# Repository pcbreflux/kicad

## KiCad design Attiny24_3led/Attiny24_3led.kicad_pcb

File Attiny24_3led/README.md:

ATtiny24 3 LED Demo
===========================
Application: kicad
Version: 5.0.0-rc2-unknown-228881f~65~ubuntu18.04.1, release build

Nightly Development Builds

	sudo add-apt-repository --yes ppa:js-reynaud/ppa-kicad
	sudo apt update
	sudo apt install kicad

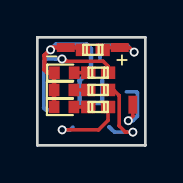
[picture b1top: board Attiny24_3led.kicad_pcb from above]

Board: 2 copper layers, 6.0 x 6.0 mm, 11 parts (1 on the bottom side), 9 nets.

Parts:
C1: C; c_0402
D1, D2, D3: LED_Small; LED_0402
J4, J5, J6: TEST_1P; SolderWirePad_single_SMD_1x0.5mm
R1, R2, R3: R; r_0402
U1: ATTINY24A-MU; QFN-20-1EP_4x4mm_Pitch0.5mm

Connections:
+3V3: C1.1, J6.1, U1.9
GND: C1.2, D1.1, D2.1, D3.1, J5.1, U1.8, U1.21
unnamed: D1.2, R1.1
unnamed: D2.2, R2.1
unnamed: D3.2, R3.1
unnamed: J4.1, U1.13
unnamed: R1.2, U1.1
unnamed: R2.2, U1.20
unnamed: R3.2, U1.16

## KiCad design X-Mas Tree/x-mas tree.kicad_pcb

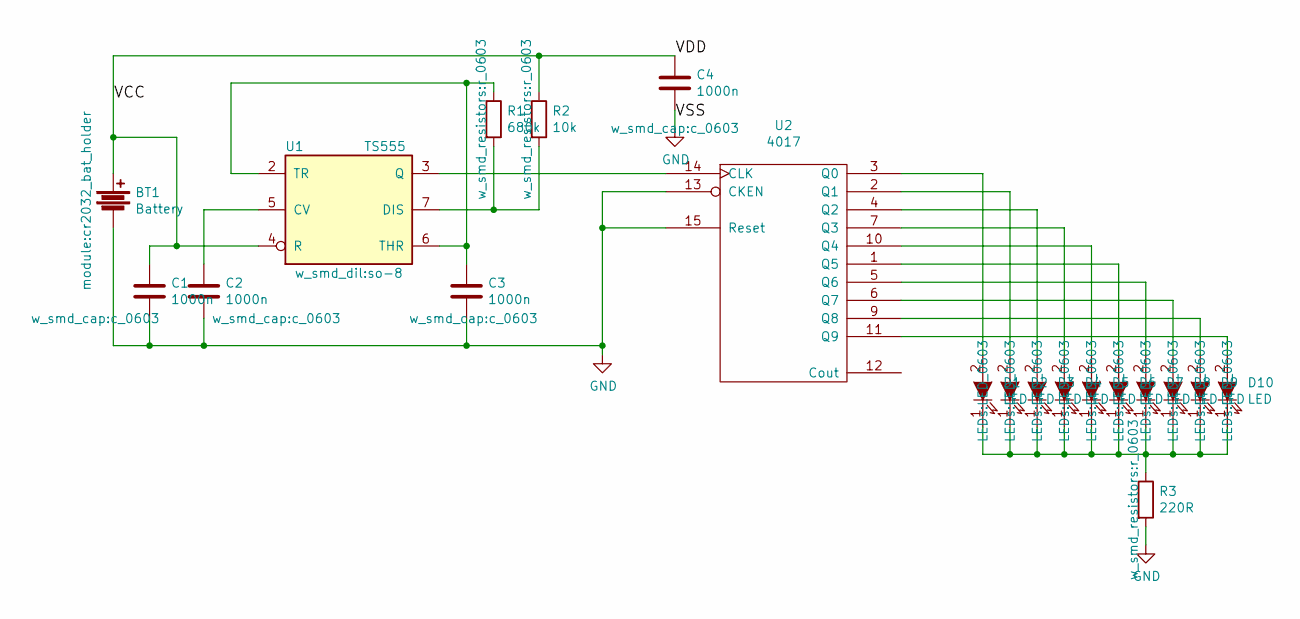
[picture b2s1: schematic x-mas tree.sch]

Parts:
BT1: Battery; cr2032_bat_holder
C1, C2, C3, C4: 1000n; c_0603
D1, D2, D3, D4, D5, D6, D7, D8, D9, D10: LED; LED_0603
R1: 680k; r_0603
R2: 10k; r_0603
R3: 220R; r_0603
U1: TS555; so-8
U2: 4017; sop-16

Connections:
GND: BT1.2, C1.2, C2.2, C3.2, C4.2, R3.2, U1.1 (GND), U2.8 (VSS), U2.13 (CKEN), U2.15 (Reset)
unnamed: C2.1, U1.5 (CV)
unnamed: C3.1, R1.1, U1.2 (TR), U1.6 (THR)
unnamed: D1.1 (K), D2.1 (K), D3.1 (K), D4.1 (K), D5.1 (K), D6.1 (K), D7.1 (K), D8.1 (K), D9.1 (K), D10.1 (K), R3.1
unnamed: D1.2 (A), U2.3 (Q0)
unnamed: D2.2 (A), U2.2 (Q1)
unnamed: D3.2 (A), U2.4 (Q2)
unnamed: D4.2 (A), U2.7 (Q3)
unnamed: D5.2 (A), U2.10 (Q4)
unnamed: D6.2 (A), U2.1 (Q5)
unnamed: D7.2 (A), U2.5 (Q6)
unnamed: D8.2 (A), U2.6 (Q7)
unnamed: D9.2 (A), U2.9 (Q8)
unnamed: D10.2 (A), U2.11 (Q9)
unnamed: R1.2, R2.2, U1.7 (DIS)
unnamed: U1.3 (Q), U2.14 (CLK)
VCC: BT1.1, C1.1, C4.1, R2.1, U1.4 (R), U1.8 (VCC), U2.16 (VDD)

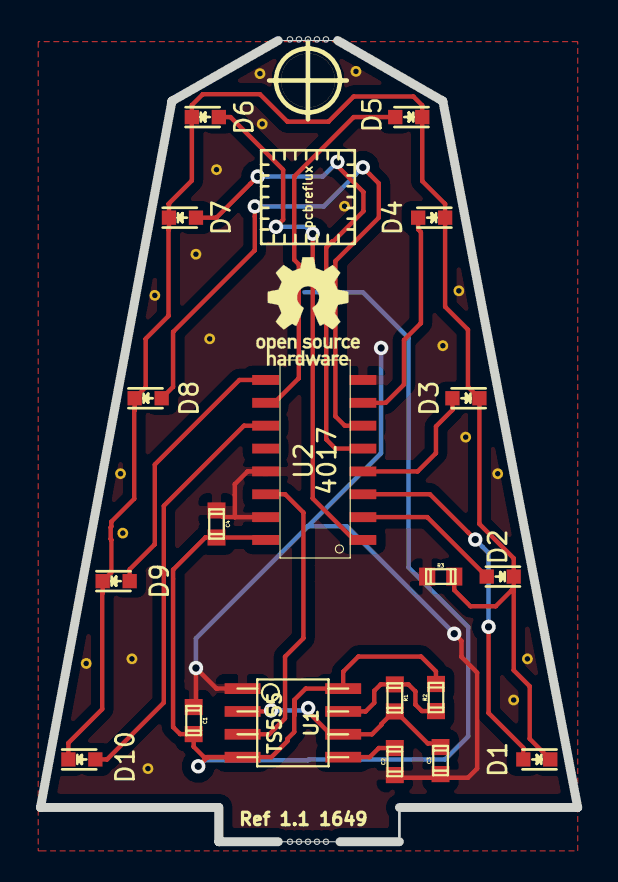
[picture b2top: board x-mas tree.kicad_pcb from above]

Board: 2 copper layers, 29.8 x 44.5 mm, 21 parts (1 on the bottom side), 17 nets.

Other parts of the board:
hole_3mm: VAL**; hole_3mm

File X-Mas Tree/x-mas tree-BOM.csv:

"Id";"Designator";"Package";"Quantity";"Designation";"Supplier and ref";
1;"U2";"sop-16";1;"4017";;;
2;"REF**";"pcbreflux_logo";1;"pcbreflux_logo";;;
3;"REF***";"OSHW-Logo_5.7x6mm_SilkScreen";1;"OSHW-Logo_5.7x6mm_SilkScreen";;;
4;"REF***";"KiCad-Logo_6mm_SilkScreen";1;"KiCad-Logo_6mm_SilkScreen";;;
5;"BT1";"cr2032_bat_holder";1;"Battery";;;
6;"REF**,REF**,REF**,REF**,REF**,REF**,REF**,REF**,REF**,REF**,REF**,REF**,REF**,REF**,REF**,REF**,REF**,REF**,REF**";"Via-0.6mm";19;"Via-0.6mm";;;
7;"hole_3mm";"hole_3mm";1;"VAL**";;;
8;"C1,C2,C4,C3";"c_0603";4;"1000n";;;
9;"D1,D2,D3,D4,D5,D6,D7,D8,D9,D10";"LED_0603";10;"LED";;;
10;"R1";"r_0603";1;"680k";;;
11;"R2";"r_0603";1;"10k";;;
12;"R3";"r_0603";1;"220R";;;
13;"U1";"so-8";1;"TS555";;;
14;"REF**,REF**";"micro_bite";2;"micro_bite";;;

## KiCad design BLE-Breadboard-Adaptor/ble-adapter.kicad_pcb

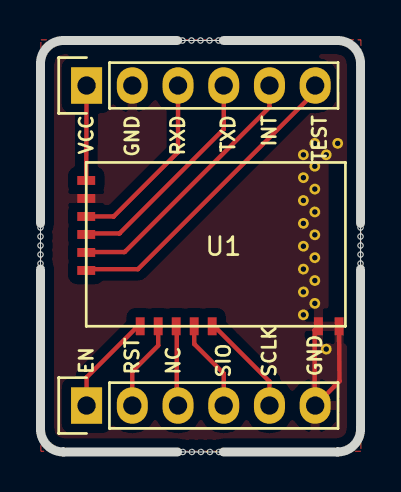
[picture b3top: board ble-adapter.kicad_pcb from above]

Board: 2 copper layers, 17.8 x 22.9 mm, 3 parts (0 on the bottom side), 11 nets.

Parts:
P1, P2: CONN_01X06; Pin_Header_Straight_1x06
U1: nRF51822-04_module; nRF51822-04_module_short

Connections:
GND: P1.2, P2.6, U1.2, U1.12, U1.13
unnamed: P1.1, U1.1
unnamed: P1.3, U1.3
unnamed: P1.4, U1.4
unnamed: P1.5, U1.5
unnamed: P1.6, U1.6
unnamed: P2.1, U1.7
unnamed: P2.2, U1.8
unnamed: P2.3, U1.9
unnamed: P2.4, U1.10
unnamed: P2.5, U1.11

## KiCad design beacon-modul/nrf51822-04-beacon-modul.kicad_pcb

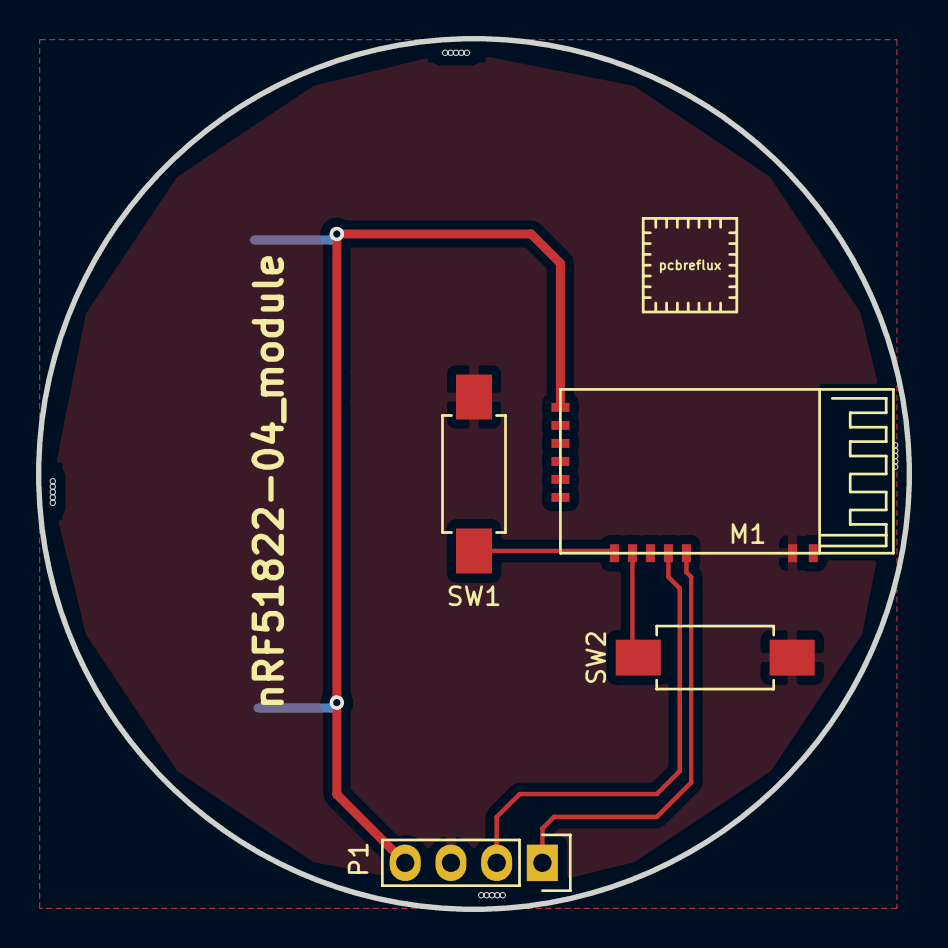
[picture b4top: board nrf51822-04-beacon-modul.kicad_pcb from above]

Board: 2 copper layers, 48.4 x 48.4 mm, 5 parts (1 on the bottom side), 6 nets.

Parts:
BT1: Battery; cr2032_bat_holder
M1: nRF51822-04_module
P1: CONN_01X04; Pin_Header_Straight_1x04
SW1, SW2: SW_PUSH_SMALL_H; SW_SPST_REED_CT05-XXXX-G1

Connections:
GND: BT1.2, M1.12, P1.3, SW1.1, SW2.1
unnamed: BT1.1, M1.1, P1.4
unnamed: M1.7, SW1.2
unnamed: M1.8, SW2.2
unnamed: M1.10, P1.2
unnamed: M1.11, P1.1

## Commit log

2016-08-19 init
2016-08-19 nur Beispiel, keine Garantie
2016-09-11 spi related
2016-09-18 Schaltplan no warrant
2016-09-20 No Warranty
2016-11-06 KiCad Gerber to Order
2016-12-06 X-Mas Tree
2016-12-28 ESP32 Adaptor
2017-09-12 KiCad to gerber
2018-06-12 Attiny24_3led
